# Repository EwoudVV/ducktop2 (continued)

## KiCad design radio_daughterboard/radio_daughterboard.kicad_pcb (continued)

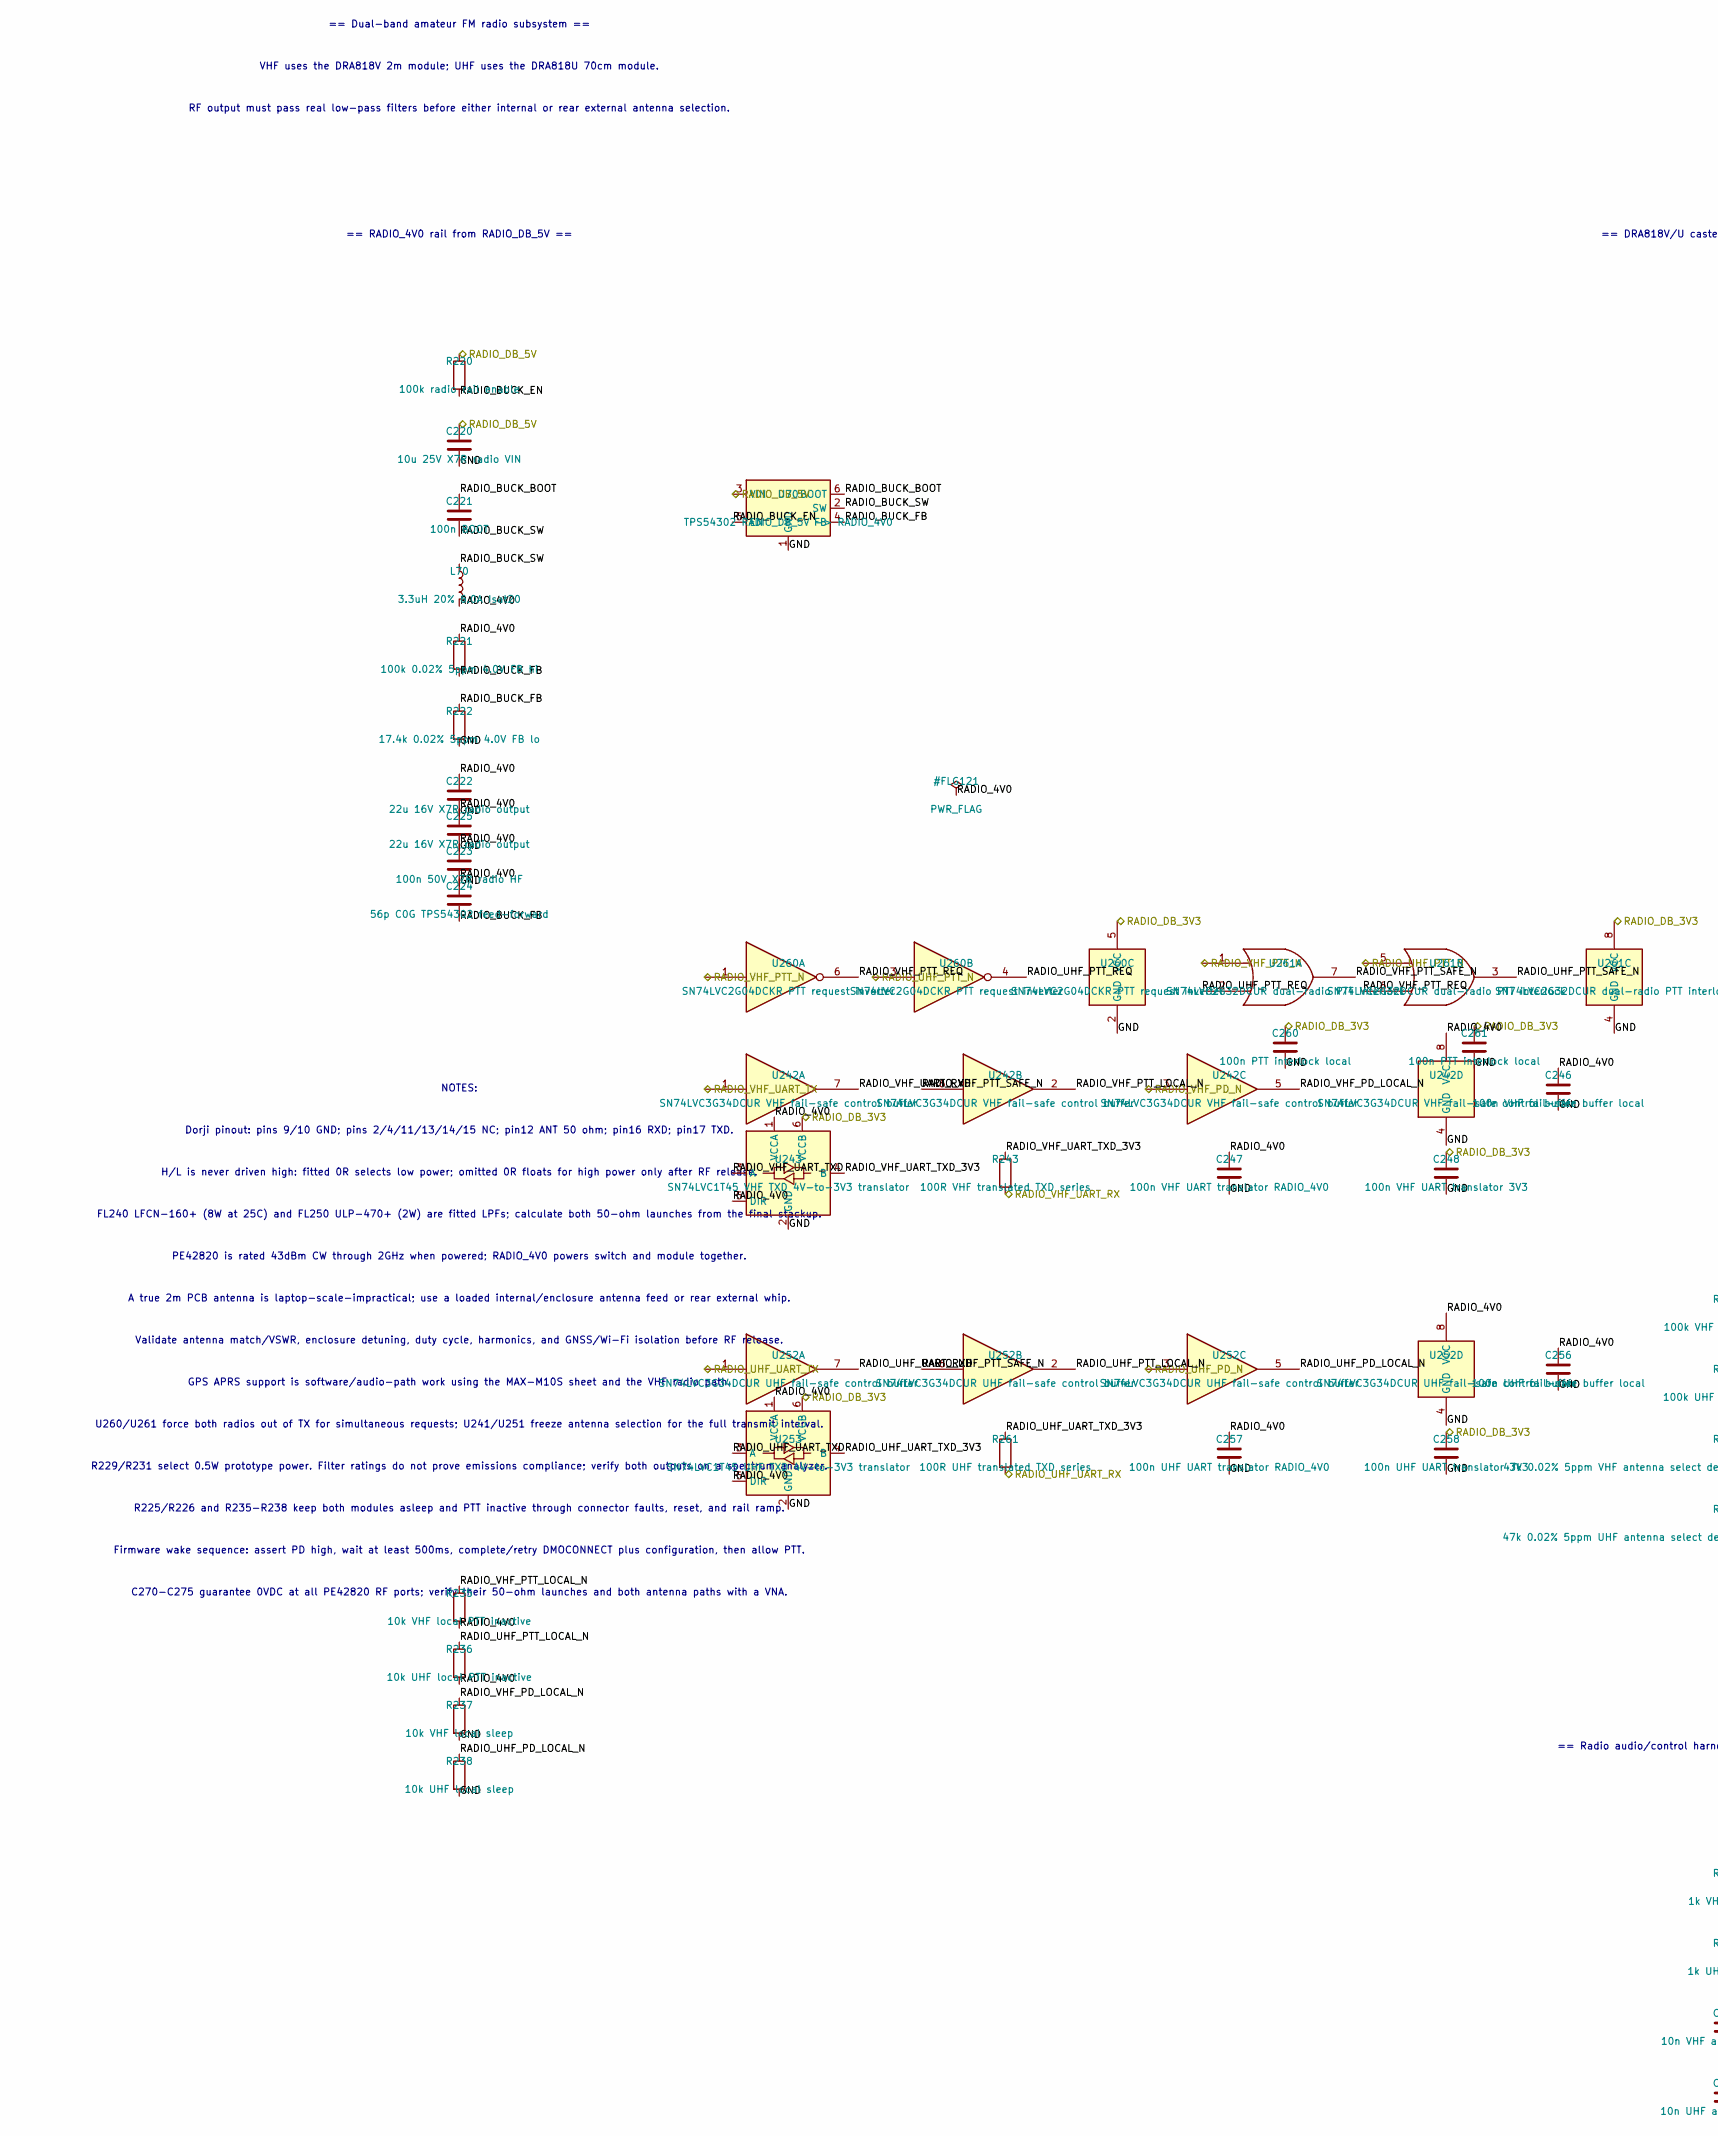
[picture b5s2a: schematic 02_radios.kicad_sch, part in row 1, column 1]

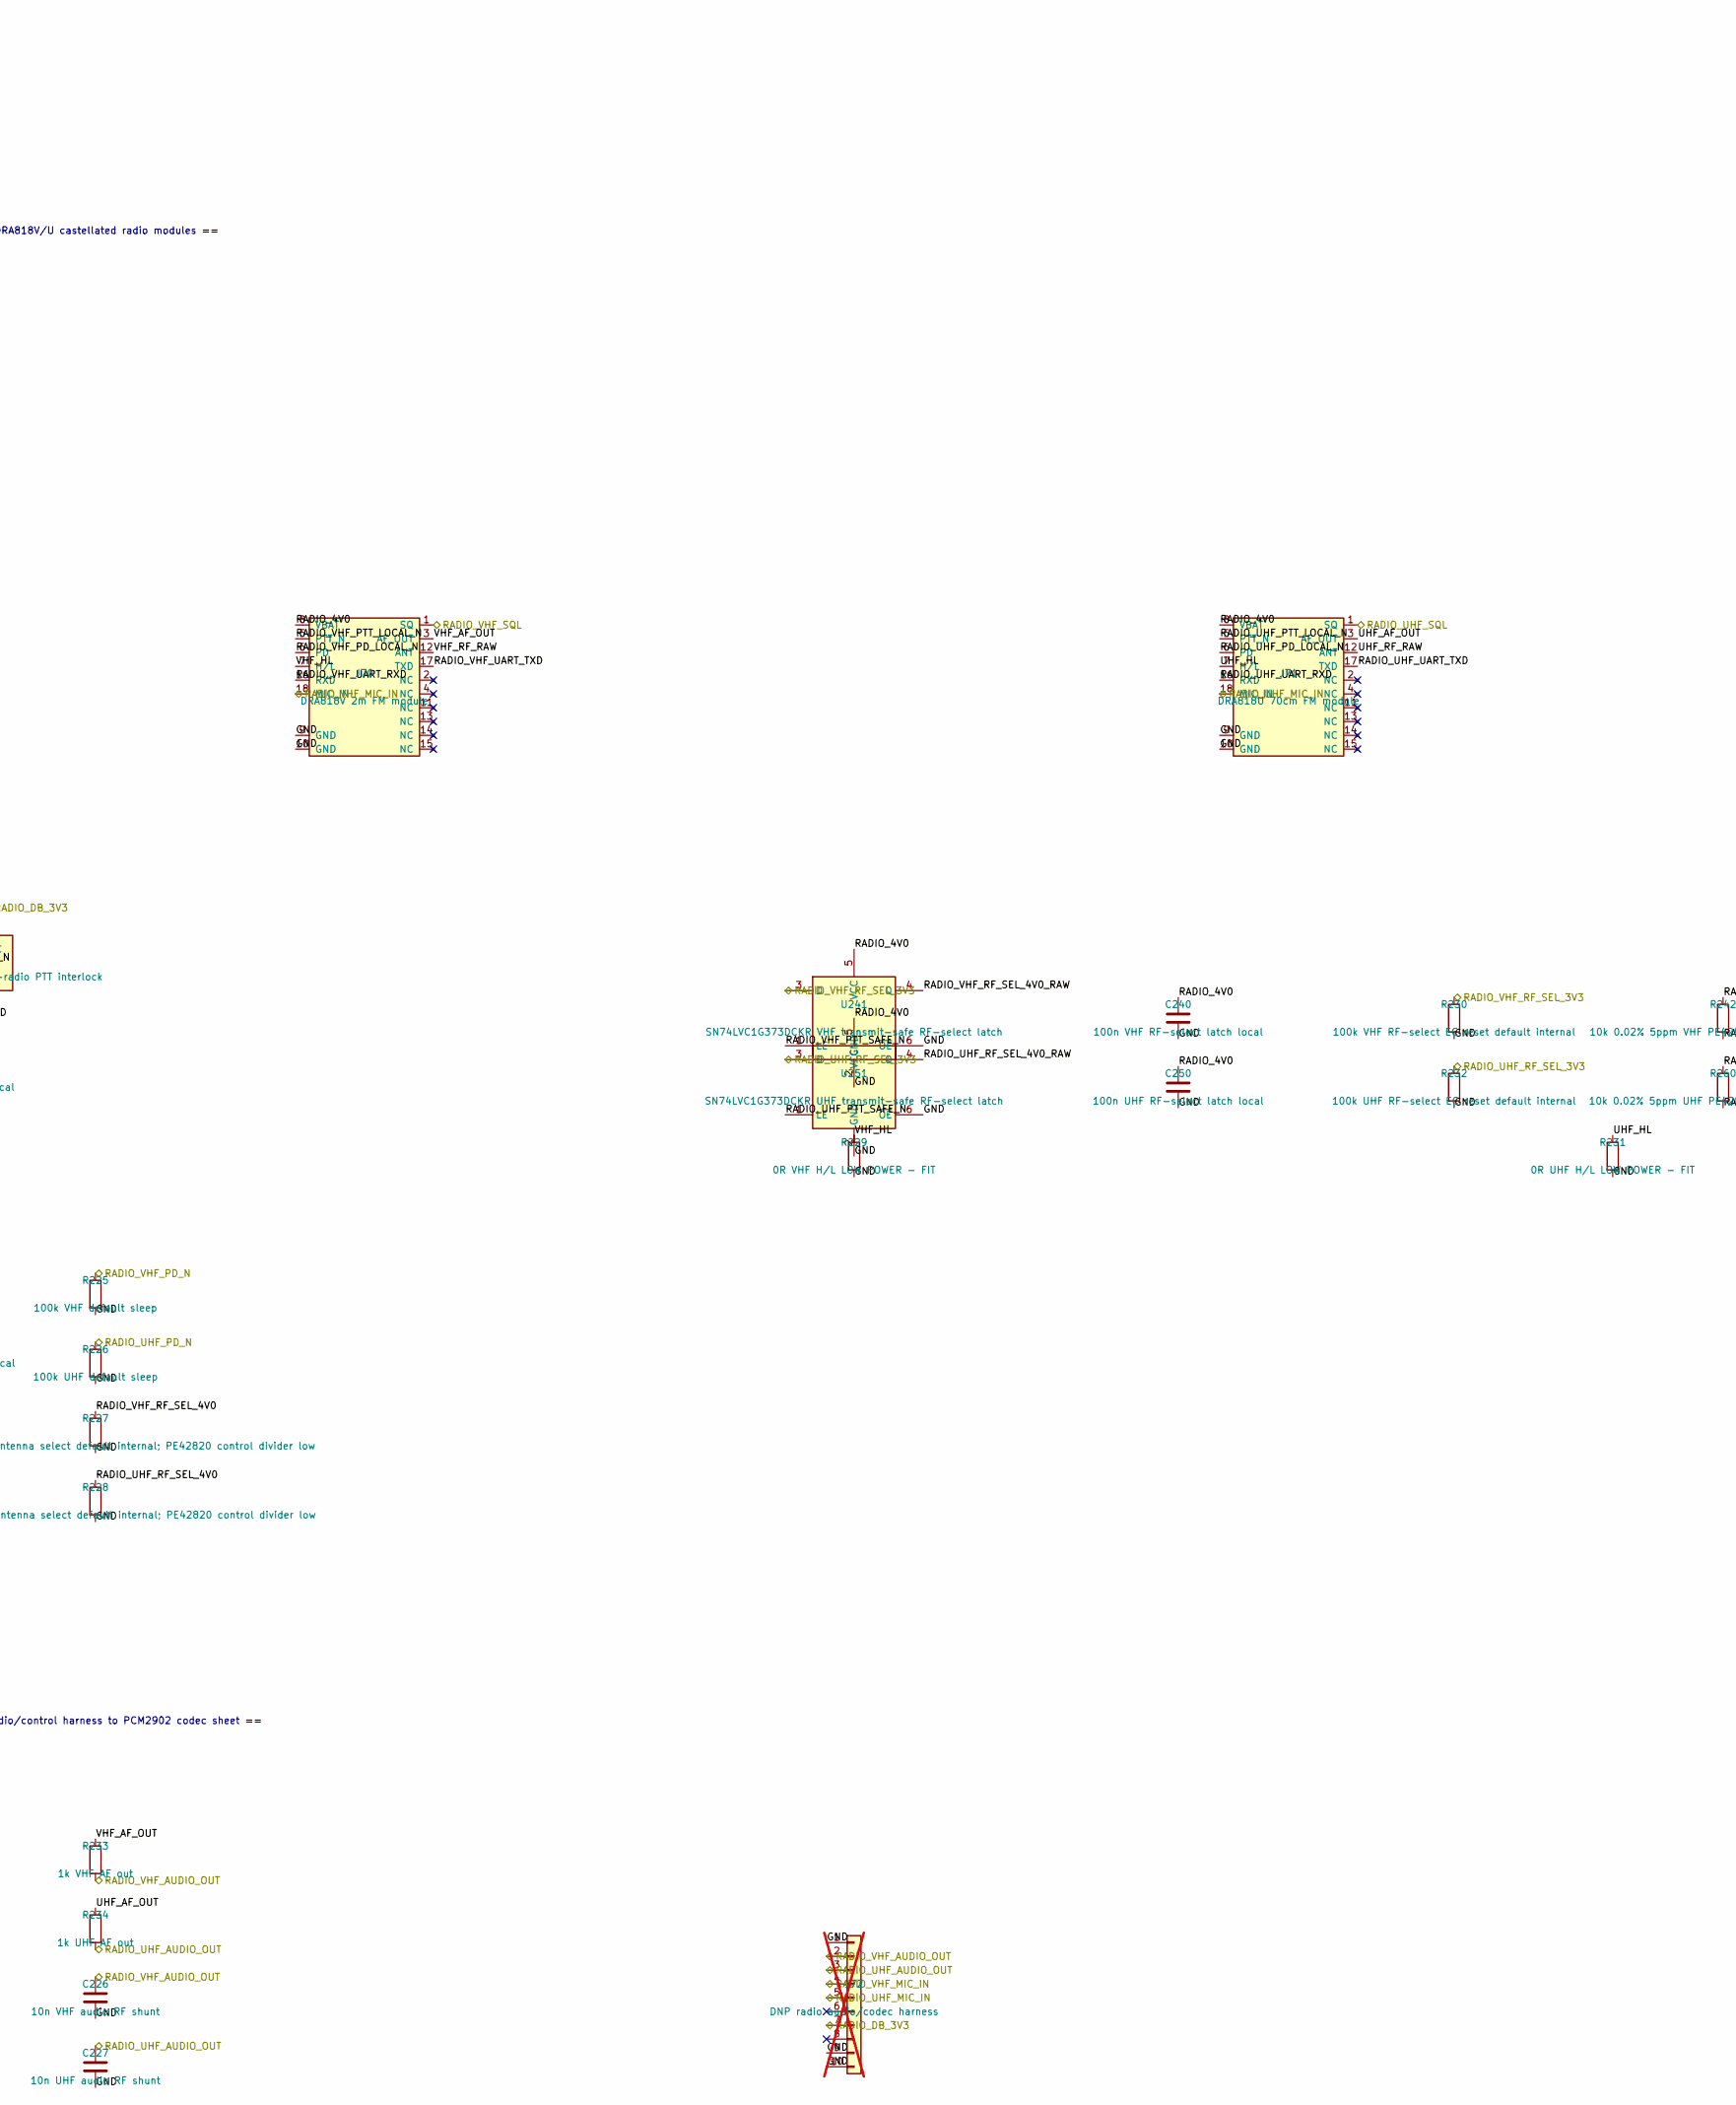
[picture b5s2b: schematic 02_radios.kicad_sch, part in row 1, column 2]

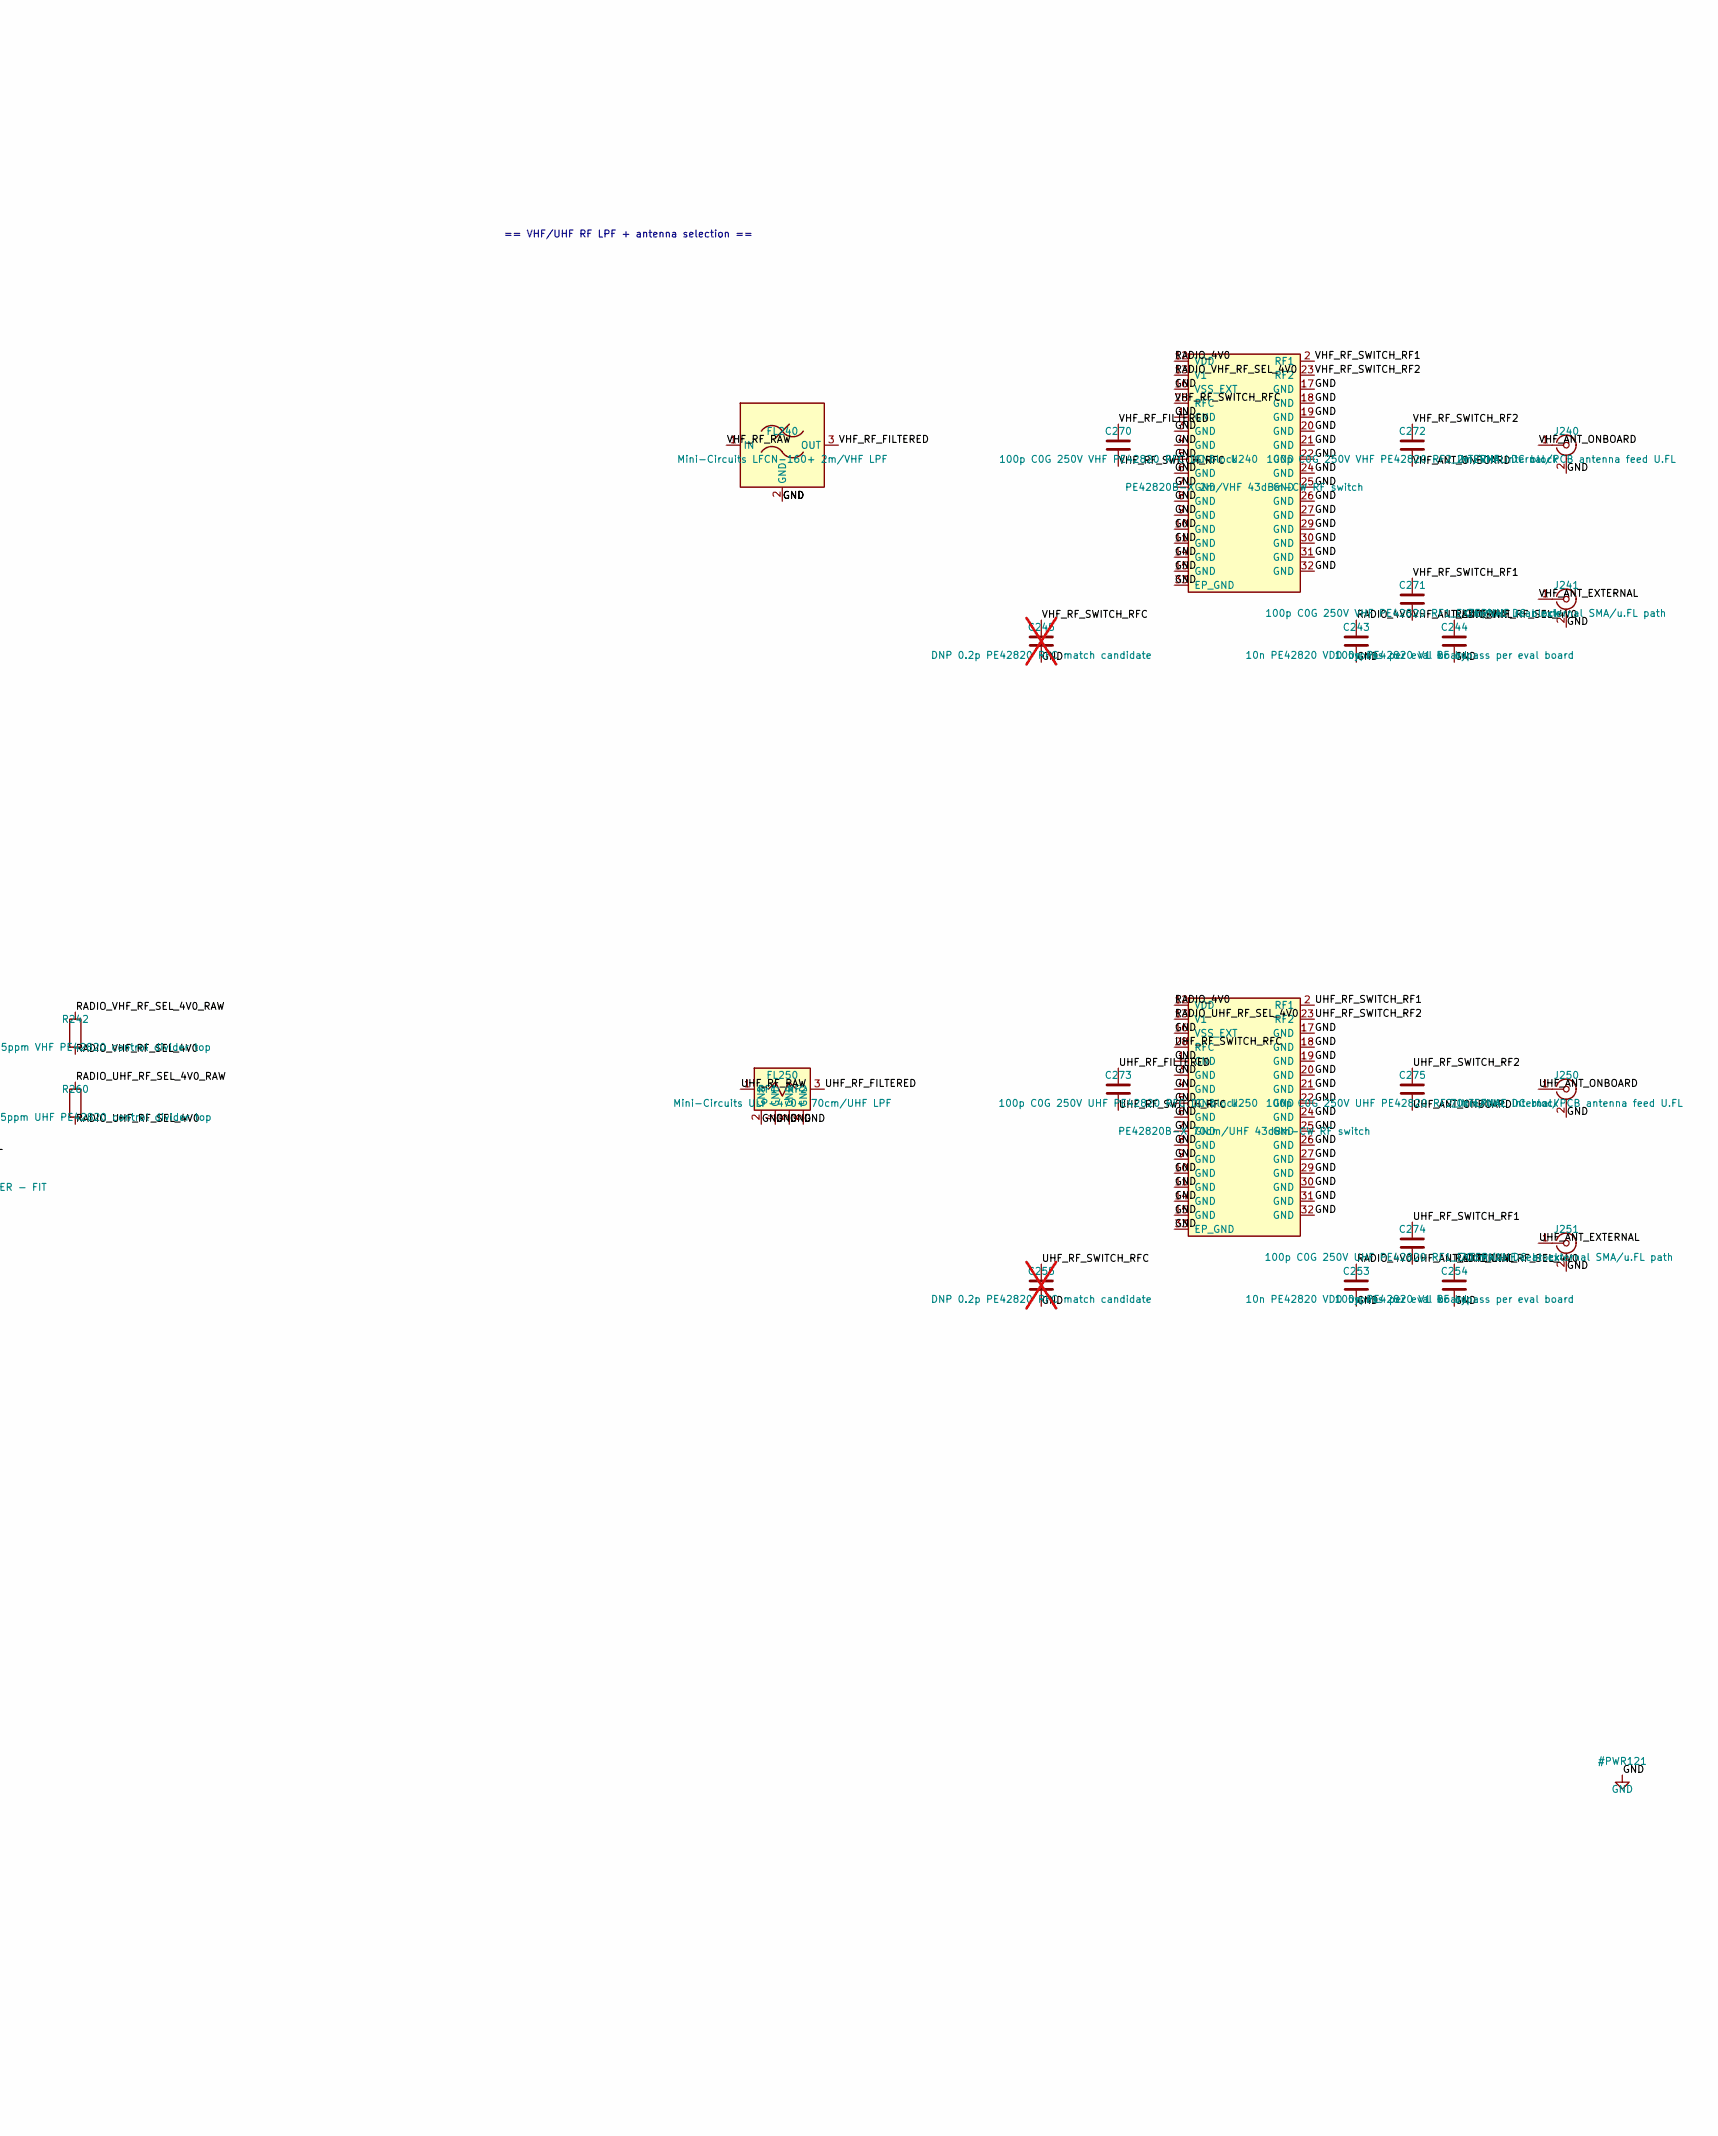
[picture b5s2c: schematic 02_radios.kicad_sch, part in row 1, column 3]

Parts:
C220: 10u 25V X7R radio VIN; C_1206_3216Metric; MPN GRM31CR71E106KA12L
C221: 100n BOOT; C_0603_1608Metric; MPN GRM188R71H104KA93D
C222, C225: 22u 16V X7R radio output; C_1206_3216Metric; MPN GRM31CZ71C226ME15L
C223: 100n 50V X7R radio HF; C_0603_1608Metric; MPN GRM188R71H104KA93D
C224: 56p C0G TPS54302 feed-forward; C_0402_1005Metric; MPN GRM1555C1H560JA01D
C226: 10n VHF audio RF shunt; C_0603_1608Metric; MPN GRM188R71H103KA01D
C227: 10n UHF audio RF shunt; C_0603_1608Metric; MPN GRM188R71H103KA01D
C240: 100n VHF RF-select latch local; C_0603_1608Metric; MPN GRM188R71H104KA93D
C243, C253: 10n PE42820 VDD bypass per eval board; C_0603_1608Metric; MPN GRM188R71H103KA01D
C244, C254: 100p PE42820 V1 RF bypass per eval board; C_0603_1608Metric; MPN GRM1885C1H101JA01D
C245, C255: DNP 0.2p PE42820 RFC match candidate; C_0603_1608Metric; not fitted
C246: 100n VHF fail-safe buffer local; C_0603_1608Metric; MPN GRM188R71H104KA93D
C247: 100n VHF UART translator RADIO_4V0; C_0603_1608Metric; MPN GRM188R71H104KA93D
C248: 100n VHF UART translator 3V3; C_0603_1608Metric; MPN GRM188R71H104KA93D
C250: 100n UHF RF-select latch local; C_0603_1608Metric; MPN GRM188R71H104KA93D
C256: 100n UHF fail-safe buffer local; C_0603_1608Metric; MPN GRM188R71H104KA93D
C257: 100n UHF UART translator RADIO_4V0; C_0603_1608Metric; MPN GRM188R71H104KA93D
C258: 100n UHF UART translator 3V3; C_0603_1608Metric; MPN GRM188R71H104KA93D
C260, C261: 100n PTT interlock local; C_0603_1608Metric; MPN GRM188R71H104KA93D
C270: 100p C0G 250V VHF PE42820 RFC DC block; C_0603_1608Metric; MPN 600S101JT250XTV
C271: 100p C0G 250V VHF PE42820 RF1_EXTERNAL DC block; C_0603_1608Metric; MPN 600S101JT250XTV
C272: 100p C0G 250V VHF PE42820 RF2_INTERNAL DC block; C_0603_1608Metric; MPN 600S101JT250XTV
C273: 100p C0G 250V UHF PE42820 RFC DC block; C_0603_1608Metric; MPN 600S101JT250XTV
C274: 100p C0G 250V UHF PE42820 RF1_EXTERNAL DC block; C_0603_1608Metric; MPN 600S101JT250XTV
C275: 100p C0G 250V UHF PE42820 RF2_INTERNAL DC block; C_0603_1608Metric; MPN 600S101JT250XTV
FL240: Mini-Circuits LFCN-160+ 2m/VHF LPF; Filter_Mini-Circuits_FV1206; MPN LFCN-160+
FL250: Mini-Circuits ULP-470+ 70cm/UHF LPF; MiniCircuits_QA2224_PL484; MPN ULP-470+
J70: DRA818V 2m FM module; DRA818_Castellated; MPN DRA818V
J71: DRA818U 70cm FM module; DRA818_Castellated; MPN DRA818U
J72: DNP radio audio/codec harness; PinHeader_1x10_P2.54mm_Vertical; not fitted
J240: 2m/VHF internal/PCB antenna feed U.FL; U.FL_Hirose_U.FL-R-SMT-1_Vertical; MPN U.FL-R-SMT-1(01)
J241: 2m/VHF rear external SMA/u.FL path; SMA_Molex_73251-1153_EdgeMount_Horizontal; MPN 73251-1153
J250: 70cm/UHF internal/PCB antenna feed U.FL; U.FL_Hirose_U.FL-R-SMT-1_Vertical; MPN U.FL-R-SMT-1(01)
J251: 70cm/UHF rear external SMA/u.FL path; SMA_Molex_73251-1153_EdgeMount_Horizontal; MPN 73251-1153
L70: 3.3uH 20% 6.0A Isat20; Coilcraft_XGL5030; MPN XGL5030-332MEC
R220: 100k radio rail enable; R_0603_1608Metric; MPN RC0603FR-07100KL
R221: 100k 0.02% 5ppm 4.0V FB hi; R_0603_1608Metric; MPN TNPU0603100KHZEN00
R222: 17.4k 0.02% 5ppm 4.0V FB lo; R_0603_1608Metric; MPN TNPU060317K4HZEN00
R225: 100k VHF default sleep; R_0603_1608Metric; MPN RC0603FR-07100KL
R226: 100k UHF default sleep; R_0603_1608Metric; MPN RC0603FR-07100KL
R227: 47k 0.02% 5ppm VHF antenna select default interna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; R_0603_1608Metric; MPN TNPU060347K0HZEN00
R228: 47k 0.02% 5ppm UHF antenna select default interna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; R_0603_1608Metric; MPN TNPU060347K0HZEN00
R229: 0R VHF H/L LOW POWER - FIT; R_0603_1608Metric; MPN RC0603FR-070RL
R230: 100k VHF RF-select EC reset default internal; R_0603_1608Metric; MPN RC0603FR-07100KL
R231: 0R UHF H/L LOW POWER - FIT; R_0603_1608Metric; MPN RC0603FR-070RL
R232: 100k UHF RF-select EC reset default internal; R_0603_1608Metric; MPN RC0603FR-07100KL
R233: 1k VHF AF out; R_0603_1608Metric; MPN RC0603FR-071KL
R234: 1k UHF AF out; R_0603_1608Metric; MPN RC0603FR-071KL
R235: 10k VHF local PTT inactive; R_0603_1608Metric; MPN RC0603FR-0710KL
R236: 10k UHF local PTT inactive; R_0603_1608Metric; MPN RC0603FR-0710KL
R237: 10k VHF local sleep; R_0603_1608Metric; MPN RC0603FR-0710KL
R238: 10k UHF local sleep; R_0603_1608Metric; MPN RC0603FR-0710KL
R242: 10k 0.02% 5ppm VHF PE42820 control divider top; R_0603_1608Metric; MPN TNPU060310K0HZEN00
R243: 100R VHF translated TXD series; R_0603_1608Metric; MPN RC0603FR-07100RL
R260: 10k 0.02% 5ppm UHF PE42820 control divider top; R_0603_1608Metric; MPN TNPU060310K0HZEN00
R261: 100R UHF translated TXD series; R_0603_1608Metric; MPN RC0603FR-07100RL
U70: TPS54302 RADIO_DB_5V -> RADIO_4V0; SOT-23-6; MPN TPS54302DDCR
U240: PE42820B-X 2m/VHF 43dBm-CW RF switch; PE42820_QFN-32-1EP_5x5mm_P0.5mm; MPN PE42820B-X
U241: SN74LVC1G373DCKR VHF transmit-safe RF-select latch; SOT-363_SC-70-6; MPN SN74LVC1G373DCKR
U242: SN74LVC3G34DCUR VHF fail-safe control buffer; VSSOP-8_2.3x2mm_P0.5mm; MPN SN74LVC3G34DCUR
U243: SN74LVC1T45 VHF TXD 4V-to-3V3 translator; SOT-23-6; MPN SN74LVC1T45DBVR
U250: PE42820B-X 70cm/UHF 43dBm-CW RF switch; PE42820_QFN-32-1EP_5x5mm_P0.5mm; MPN PE42820B-X
U251: SN74LVC1G373DCKR UHF transmit-safe RF-select latch; SOT-363_SC-70-6; MPN SN74LVC1G373DCKR
U252: SN74LVC3G34DCUR UHF fail-safe control buffer; VSSOP-8_2.3x2mm_P0.5mm; MPN SN74LVC3G34DCUR
U253: SN74LVC1T45 UHF TXD 4V-to-3V3 translator; SOT-23-6; MPN SN74LVC1T45DBVR
U260: SN74LVC2G04DCKR PTT request inverter; SOT-363_SC-70-6; MPN SN74LVC2G04DCKR
U261: SN74LVC2G32DCUR dual-radio PTT interlock; VSSOP-8_2.3x2mm_P0.5mm; MPN SN74LVC2G32DCUR

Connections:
/RADIO_DB_3V3: C248.1, C258.1, C260.1, C261.1, J72.7, U243.6 (VCCB), U253.6 (VCCB), U260.5 (VCC), U261.8 (VCC); also elsewhere on the board
/RADIO_DB_5V: C220.1, R220.1, U70.3 (VIN); also elsewhere on the board
/RADIO_UHF_AUDIO_OUT: C227.1, J72.3, R234.2; also elsewhere on the board
/RADIO_UHF_MIC_IN: J71.18 (MIC_IN), J72.5; also elsewhere on the board
/RADIO_UHF_PD_N: R226.1, U252.3; also elsewhere on the board
/RADIO_UHF_PTT_N: U260.3, U261.5; also elsewhere on the board
/RADIO_UHF_RF_SEL_3V3: R232.1, U251.3 (D); also elsewhere on the board
/RADIO_UHF_SQL: J71.1 (SQ); also elsewhere on the board
/RADIO_UHF_UART_RX: R261.2; also elsewhere on the board
/RADIO_UHF_UART_TX: U252.1; also elsewhere on the board
/RADIO_VHF_AUDIO_OUT: C226.1, J72.2, R233.2; also elsewhere on the board
/RADIO_VHF_MIC_IN: J70.18 (MIC_IN), J72.4; also elsewhere on the board
/RADIO_VHF_PD_N: R225.1, U242.3; also elsewhere on the board
/RADIO_VHF_PTT_N: U260.1, U261.1; also elsewhere on the board
/RADIO_VHF_RF_SEL_3V3: R230.1, U241.3 (D); also elsewhere on the board
/RADIO_VHF_SQL: J70.1 (SQ); also elsewhere on the board
/RADIO_VHF_UART_RX: R243.2; also elsewhere on the board
/RADIO_VHF_UART_TX: U242.1; also elsewhere on the board
/VHF & UHF Radios/RADIO_4V0: C222.1, C223.1, C224.1, C225.1, C240.1, C243.1, C246.1, C247.1, C250.1, C253.1, C256.1, C257.1, J70.8 (VBAT), J71.8 (VBAT), L70.2, R221.1, R235.2, R236.2, U240.12 (VDD), U241.5 (VCC), U242.8 (VCC), U243.1 (VCCA), U243.5 (DIR), U250.12 (VDD), U251.5 (VCC), U252.8 (VCC), U253.1 (VCCA), U253.5 (DIR)
/VHF & UHF Radios/RADIO_BUCK_BOOT: C221.1, U70.6 (BOOT)
/VHF & UHF Radios/RADIO_BUCK_EN: R220.2, U70.5 (EN)
/VHF & UHF Radios/RADIO_BUCK_FB: C224.2, R221.2, R222.1, U70.4 (FB)
/VHF & UHF Radios/RADIO_BUCK_SW: C221.2, L70.1, U70.2 (SW)
/VHF & UHF Radios/RADIO_UHF_PD_LOCAL_N: J71.6 (PD), R238.1, U252.5
/VHF & UHF Radios/RADIO_UHF_PTT_LOCAL_N: J71.5 (PTT_N), R236.1, U252.2
/VHF & UHF Radios/RADIO_UHF_PTT_REQ: U260.4, U261.2
/VHF & UHF Radios/RADIO_UHF_PTT_SAFE_N: U251.1 (LE), U252.6, U261.3
/VHF & UHF Radios/RADIO_UHF_RF_SEL_4V0: C254.1, R228.1, R260.2, U250.13 (V1)
/VHF & UHF Radios/RADIO_UHF_RF_SEL_4V0_RAW: R260.1, U251.4 (Q)
/VHF & UHF Radios/RADIO_UHF_UART_RXD: J71.16 (RXD), U252.7
/VHF & UHF Radios/RADIO_UHF_UART_TXD: J71.17 (TXD), U253.3 (A)
/VHF & UHF Radios/RADIO_UHF_UART_TXD_3V3: R261.1, U253.4 (B)
/VHF & UHF Radios/RADIO_VHF_PD_LOCAL_N: J70.6 (PD), R237.1, U242.5
/VHF & UHF Radios/RADIO_VHF_PTT_LOCAL_N: J70.5 (PTT_N), R235.1, U242.2
/VHF & UHF Radios/RADIO_VHF_PTT_REQ: U260.6, U261.6
/VHF & UHF Radios/RADIO_VHF_PTT_SAFE_N: U241.1 (LE), U242.6, U261.7
/VHF & UHF Radios/RADIO_VHF_RF_SEL_4V0: C244.1, R227.1, R242.2, U240.13 (V1)
/VHF & UHF Radios/RADIO_VHF_RF_SEL_4V0_RAW: R242.1, U241.4 (Q)
/VHF & UHF Radios/RADIO_VHF_UART_RXD: J70.16 (RXD), U242.7
/VHF & UHF Radios/RADIO_VHF_UART_TXD: J70.17 (TXD), U243.3 (A)
/VHF & UHF Radios/RADIO_VHF_UART_TXD_3V3: R243.1, U243.4 (B)
/VHF & UHF Radios/UHF_AF_OUT: J71.3 (AF_OUT), R234.1
/VHF & UHF Radios/UHF_ANT_EXTERNAL: C274.2, J251.1 (In)
/VHF & UHF Radios/UHF_ANT_ONBOARD: C275.2, J250.1 (In)
/VHF & UHF Radios/UHF_HL: J71.7 (H/L), R231.1
/VHF & UHF Radios/UHF_RF_FILTERED: C273.1, FL250.3 (RF2)
/VHF & UHF Radios/UHF_RF_RAW: FL250.1 (RF1), J71.12 (ANT)
/VHF & UHF Radios/UHF_RF_SWITCH_RF1: C274.1, U250.2 (RF1)
/VHF & UHF Radios/UHF_RF_SWITCH_RF2: C275.1, U250.23 (RF2)
/VHF & UHF Radios/UHF_RF_SWITCH_RFC: C255.1, C273.2, U250.28 (RFC)
/VHF & UHF Radios/VHF_AF_OUT: J70.3 (AF_OUT), R233.1
/VHF & UHF Radios/VHF_ANT_EXTERNAL: C271.2, J241.1 (In)
/VHF & UHF Radios/VHF_ANT_ONBOARD: C272.2, J240.1 (In)
/VHF & UHF Radios/VHF_HL: J70.7 (H/L), R229.1
/VHF & UHF Radios/VHF_RF_FILTERED: C270.1, FL240.3 (OUT)
/VHF & UHF Radios/VHF_RF_RAW: FL240.1 (IN), J70.12 (ANT)
/VHF & UHF Radios/VHF_RF_SWITCH_RF1: C271.1, U240.2 (RF1)
/VHF & UHF Radios/VHF_RF_SWITCH_RF2: C272.1, U240.23 (RF2)
/VHF & UHF Radios/VHF_RF_SWITCH_RFC: C245.1, C270.2, U240.28 (RFC)
GND: C220.2, C222.2, C223.2, C225.2, C226.2, C227.2, C240.2, C243.2, C244.2, C245.2, C246.2, C247.2, C248.2, C250.2, C253.2, C254.2, C255.2, C256.2, C257.2, C258.2, C260.2, C261.2, FL240.2 (GND), FL240.4 (GND), FL250.2 (GND), FL250.4 (GND), FL250.5 (GND), FL250.6 (GND), J70.9 (GND), J70.10 (GND), J71.9 (GND), J71.10 (GND), J72.1, J72.9, J72.10, J240.2 (Ext), J241.2 (Ext), J250.2 (Ext), J251.2 (Ext), R222.2, R225.2, R226.2, R227.2, R228.2, R229.2, R230.2, R231.2, R232.2, R237.2, R238.2, U70.1 (GND), U240.1 (GND), U240.3 (GND), U240.4 (GND), U240.5 (GND), U240.6 (GND), U240.7 (GND), U240.8 (GND), U240.9 (GND), U240.10 (GND), U240.11 (GND), U240.14 (GND), U240.15 (GND), U240.16 (VSS_EXT), U240.17 (GND), U240.18 (GND), U240.19 (GND), U240.20 (GND), U240.21 (GND), U240.22 (GND), U240.24 (GND), U240.25 (GND), U240.26 (GND), U240.27 (GND), U240.29 (GND), U240.30 (GND), U240.31 (GND), U240.32 (GND), U240.33 (EP_GND), U241.2 (GND), U241.6 (~OE), U242.4 (GND), U243.2 (GND), U250.1 (GND), U250.3 (GND), U250.4 (GND), U250.5 (GND), U250.6 (GND), U250.7 (GND), U250.8 (GND), U250.9 (GND), U250.10 (GND), U250.11 (GND), U250.14 (GND), U250.15 (GND), U250.16 (VSS_EXT), U250.17 (GND), U250.18 (GND), U250.19 (GND), U250.20 (GND), U250.21 (GND), U250.22 (GND), U250.24 (GND), U250.25 (GND), U250.26 (GND), U250.27 (GND), U250.29 (GND), U250.30 (GND), U250.31 (GND), U250.32 (GND), U250.33 (EP_GND), U251.2 (GND), U251.6 (~OE), U252.4 (GND), U253.2 (GND), U260.2 (GND), U261.4 (GND); also elsewhere on the board

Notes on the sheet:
== Dual-band amateur FM radio subsystem ==
VHF uses the DRA818V 2m module; UHF uses the DRA818U 70cm module.
RF output must pass real low-pass filters before either internal or rear external antenna selection.
== RADIO_4V0 rail from RADIO_DB_5V ==
== DRA818V/U castellated radio modules ==
== Radio audio/control harness to PCM2902 codec sheet ==
== VHF/UHF RF LPF + antenna selection ==
NOTES:
Dorji pinout: pins 9/10 GND; pins 2/4/11/13/14/15 NC; pin12 ANT 50 ohm; pin16 RXD; pin17 TXD.
H/L is never driven high: fitted 0R selects low power; omitted 0R floats for high power only after RF release.
FL240 LFCN-160+ (8W at 25C) and FL250 ULP-470+ (2W) are fitted LPFs; calculate both 50-ohm launches from the final stackup.
PE42820 is rated 43dBm CW through 2GHz when powered; RADIO_4V0 powers switch and module together.
A true 2m PCB antenna is laptop-scale-impractical; use a loaded internal/enclosure antenna feed or rear external whip.
Validate antenna match/VSWR, enclosure detuning, duty cycle, harmonics, and GNSS/Wi-Fi isolation before RF release.
GPS APRS support is software/audio-path work using the MAX-M10S sheet and the VHF radio path.
U260/U261 force both radios out of TX for simultaneous requests; U241/U251 freeze antenna selection for the full transmit interval.
R229/R231 select 0.5W prototype power. Filter ratings do not prove emissions compliance; verify both outputs on a spectrum analyzer.
R225/R226 and R235-R238 keep both modules asleep and PTT inactive through connector faults, reset, and rail ramp.
Firmware wake sequence: assert PD high, wait at least 500ms, complete/retry DMOCONNECT plus configuration, then allow PTT.
C270-C275 guarantee 0VDC at all PE42820 RF ports; verify their 50-ohm launches and both antenna paths with a VNA.
